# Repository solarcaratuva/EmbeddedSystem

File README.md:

# UVA Solar Car Team Electrical Team - Embedded System Subgroup
The embedded system sub-group focuses on developing the embedded system for the solar car that controls the CAN bus, driver interface and BPS (Battery Management System). This repository contains all of the design files necessary to implement the electrical control systems necessary for the Solar Car project.

## ECU
The ECU is the primary controller for the majority of systems, including motor control, battery monitoring, driver interface, and MPPT interface. The PCB contains circuitry for interfacing buttons and switches on driver interface, high-current lights and horn, as well as

**!important!**
Not all pins are 12V or even 5V compatible. Certain pins connect directly to the teensy with no protection.

* signal: name of IO signal in Eeschema (may or may not also be the net name)
* voltage: the voltages the pin is designed for
* direction: The direction of the signal relative to the ECU
* description: description of the signal

### User interface input (control)
These pins are used for allowing the driver to command the vehicle. All but the UART pins are 12V logic. To reduce the number of pins required on the MCU, we chose to wire 3 way position switches such that the end contacts connect to the rails and the center contact floats with a resistor divider to ensure the voltage is approximately VCC/2 when the switch is in the middle position.

|      signal     | pin  | voltage  | direction |                            description                               |
|:---------------:|:----:|:--------:|:---------:|:--------------------------------------------------------------------:|
| BRAKE_CTRL      |  20  | 0 - 12V  |  input    | brake potentiometer, used to implement regen                         |
| REGEN_CTRL      |  17  | 0 - 12V  |  input    | regen potentiometer, used to set max regen percentage                |
| GEARSHIFT_CTRL  |  14  | 0 - 12V  |  input    | 3 way position switch. 12V = forward, 6V = neutral, 0V = reverse     |
| TURNSIG_CTRL    |  15  | 0 - 12V  |  input    | 3 way position switch. 12V = forward, 6V = neutral, 0V = reverse     |
| THROTTLE_CTRL   |  16  | 0 - 12V  |  input    | throttle potentiometer, the gas petal                                |
| STEER_CTRL      |21(A7)| 0 - 12V  |  input    | potentiometer on steering wheel, may be used for differential throttle control |
| HAZARD_CTRL     |  16  | 0 - 12V  |  input    | pushbutton used to activate hazard lights, toggles on changing edge  |
| HORN_CTRL       |22(A6)| 0 - 12V  |  input    | horn button                                                          |
| DOWN_CTRL       |  26  | 0 - 12V  |  input    | GUI navigation pushbutton                                            |
| UP_CTRL         |  27  | 0 - 12V  |  input    | GUI navigation pushbutton                                            |
| SEL_CTRL        |  28  | 0 - 12V  |  input    | GUI navigation pushbutton                                            |
| KILL_SENSE      |   2  | 0 - 12V  |  input    | used to detect if the power engaging the relays has been cut         |
| HAZARD_LED      |  25  | 0 - 12V  |  output   | connected to hazard button LED                                       |
| UART_1_RX       |   0  | 0 - 3.3V |  input    | used for Nextion 3.2" LCD                                            |
| UART_1_TX       |   1  | 0 - 3.3V |  output   | used for Nextion 3.2" LCD                                            |

### Serial interface IO
These pins are used for communicating with various peripherals, components, and subsystems within the car. CAN0 is reserved for the BMS, while CAN1 is used for all less critical systems. UART pins are for future use.

|      signal     |  pin    | voltage  | direction |                            description                               |
|:---------------:|:-------:|:--------:|:---------:|:--------------------------------------------------------------------:|
| CAN0_H          |         | 0 - 5V   | CAN high  | connected to CAN0 peripheral on Teensy 3.6 through MCP2562           |
| CAN0_L          |         | 0 - 5V   | CAN low   | connected to CAN0 peripheral on Teensy 3.6 through MCP2562           |
| CAN1_H          |         | 0 - 5V   | CAN high  | connected to CAN1 peripheral on Teensy 3.6 through MCP2562           |
| CAN1_L          |         | 0 - 5V   | CAN low   | connected to CAN1 peripheral on Teensy 3.6 through MCP2562           |
| UART_3_RX       |    7    | 0 - 3.3V |  input    | reserved for future use                                              |
| UART_3_TX       |    8    | 0 - 3.3V |  output   | reserved for future use                                              |
| UART_6_RX       |   47    | 0 - 3.3V |  input    | reserved for future use                                              |
| UART_6_TX       |   48    | 0 - 3.3V |  output   | reserved for future use                                              |

### Lights and Horn
These pins are capable of high currents (up to 5A distributed among the 4 outputs)

|      signal     |   pin    | voltage  | direction |                            description                               |
|:---------------:|:--------:|:--------:|:---------:|:--------------------------------------------------------------------:|
| HORN            |    57    | 0 - 12V  |   output  | high power output for car horn (can only source current)             |
| HEADLIGHTS      |    42    | 0 - 12V  |   output  | high power output for headlights (can only source current)           |
| BRAKELIGHTS     |    56    | 0 - 12V  |   output  | high power output for brakelights (can only source current)          |
| STROBE          |    6     | 0 - 12V  |   output  | high power output for strobelight (can only source current)          |
| RIGHT_BLINKERS  |    41    | 0 - 12V  |   output  | high power output for right blinkers (can only source current)       |
| LEFT_BLINKERS   |    40    | 0 - 12V  |   output  | high power output for left blinkers (can only source current)        |
| HORN_CTRL       |    22    | 0 - 12V  |   input   | high power input for horn                                            |
| HEADLIGHT_CTRL  |    23    | 0 - 12V  |   input   | high power input for headlights                                      |
| BRAKE_CTRL      |    20    | 0 - 12v  |   input   | analog input for brakes (used for regen)                             |

### Motor control
The motor can be interfaced via UART, CAN, and GPIO. As of now, we do not have any API or knowledge of how to interface the motor over UART, as it is not documented. However it is possible to decompile the android app and reverse engineer whatever the app implements. For now, we are using CAN to retrieve important parameters from the motor such as voltage, current, RPM, throttle, and error codes. The motor only outputs messages over CAN, and does not interpret them.

The table below holds true for both `MOTOR_R*` and `MOTOR_L*` signals.
NOTE: all node names in the table below are preceded with `MOTOR_R*` and `MOTOR_L*`!

|      signal     | pin (L) | pin (R) |  voltage   | direction |                               description                            |
|:---------------:|:--------|:-------:|:----------:|:---------:|:--------------------------------------------------------------------:|
| REGEN_EN        |   50    |   53    |   0 - 12V  |   output  | enables regenerative braking on motor controller                     |
| REGEN           | 36(pwm) | 37(pwm) |   0 - 5V   |   output  | analog output sets regen level when throttle is disabled (????)      |
| THROTTLE        | 35(pwm) | 38(pwm) |   0 - 5V   |   output  | sets throttle when FWD_EN or REV_EN are enabled.                     |
| ECO_EN          |   49    |   39    |   0 - 12V  |   output  | Reduces maximum power of motor controller                            |
| METER           |   A11   |   A10   |   0 - 12V  |   input   | analog output from motor controller (????)                           |
| FWD_EN          |   55    |   52    |   0 - 12V  |   output  | forward enable                                                       |
| REV_EN          |   54    |   51    |   0 - 12V  |   output  | reverse enable                                                       |

## Software
At the moment we have bits and pieces of code written but no unified project as of yet. The CAN repository contains experemantal code for interfacing the CAN peripherals on the Teensy as well as development towards a motor driver. The completed motor driver will eventually be refactored into this repo.

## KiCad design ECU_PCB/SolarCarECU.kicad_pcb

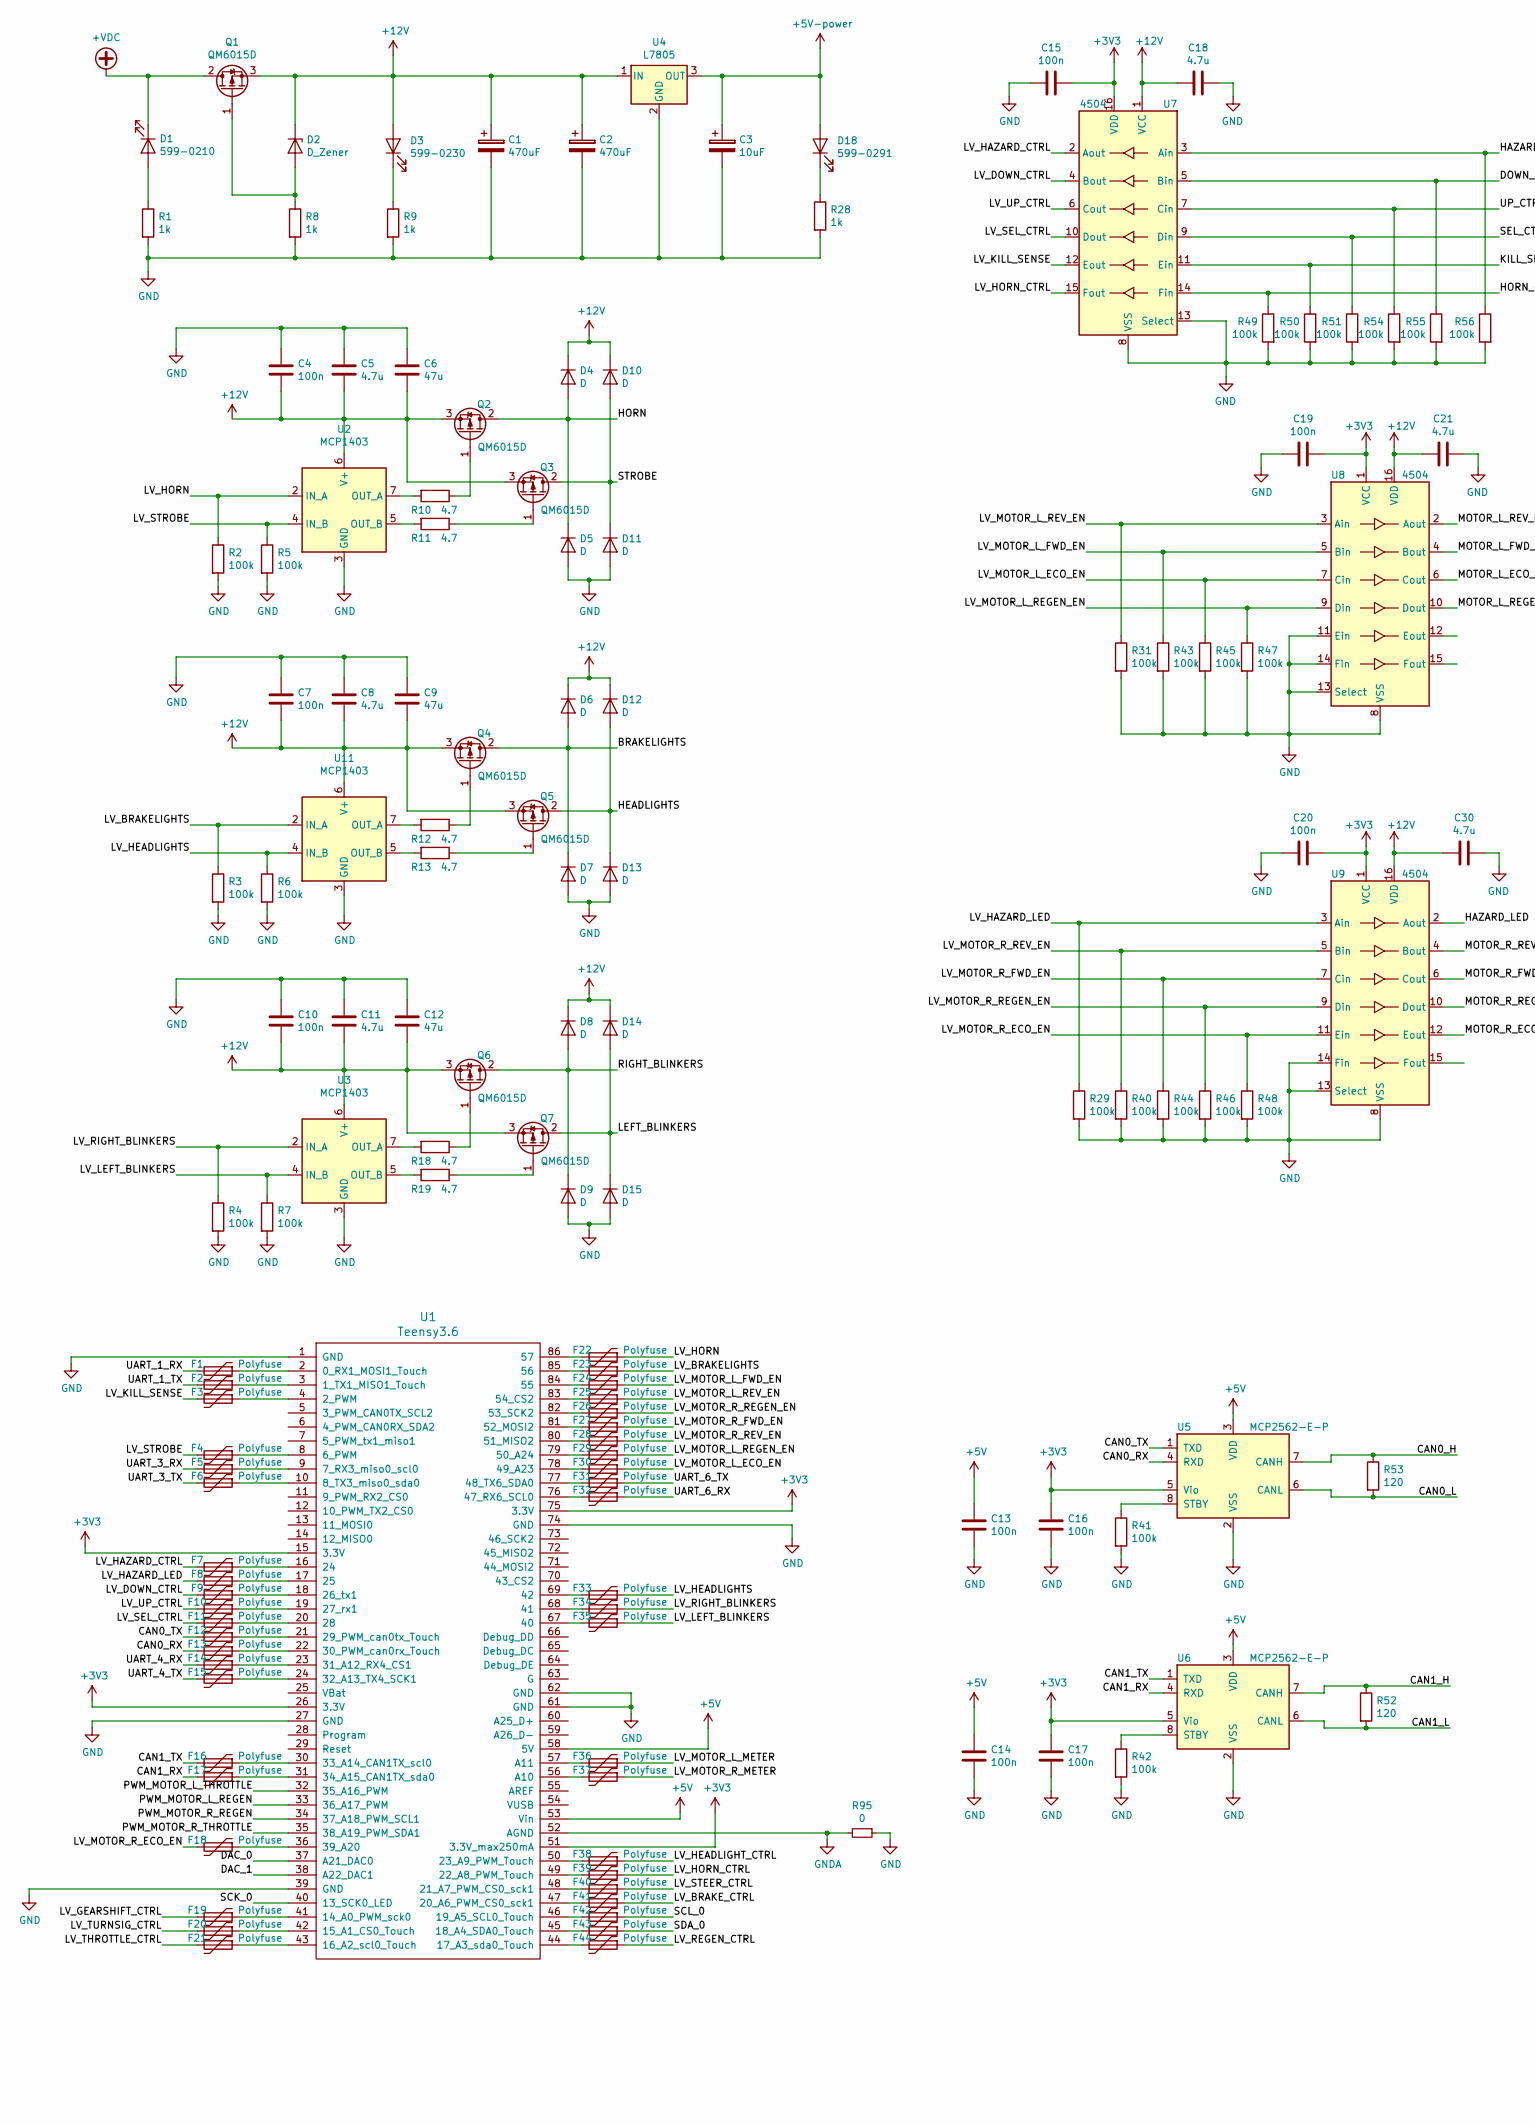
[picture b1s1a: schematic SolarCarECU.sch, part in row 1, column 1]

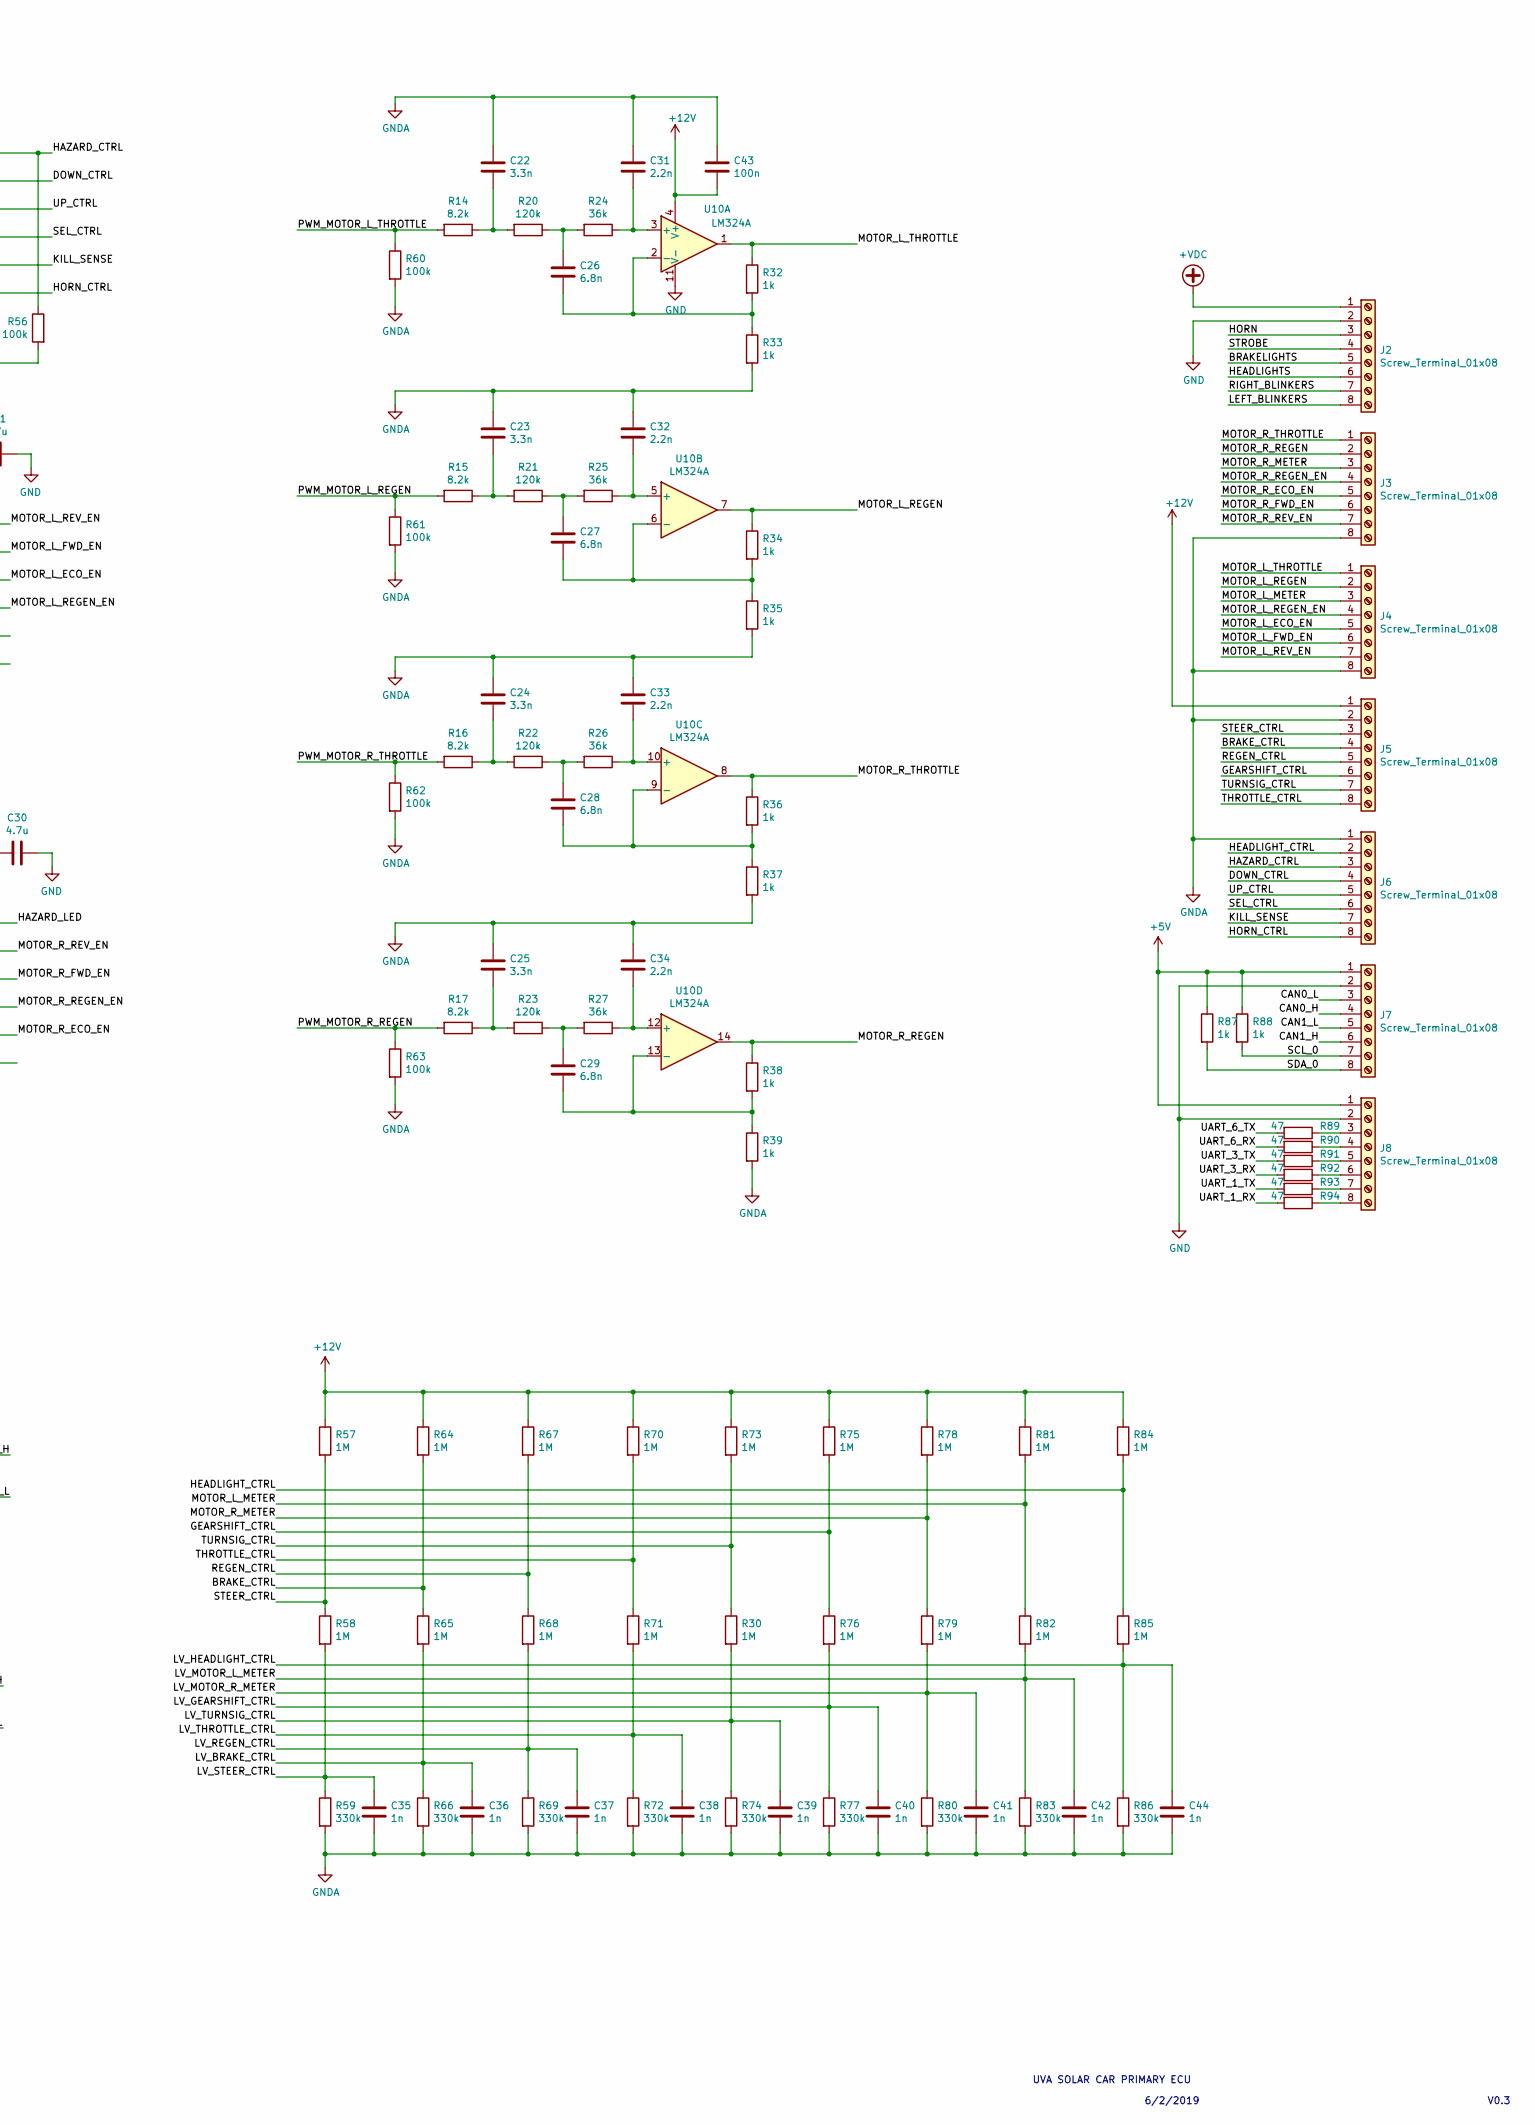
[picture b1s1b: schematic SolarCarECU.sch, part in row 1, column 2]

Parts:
C1, C2: 470uF; CP_Radial_D13.0mm_P5.00mm
C3: 10uF; C_1206_3216Metric
C4, C7, C10, C13, C14, C15, C16, C17, C19, C20, C43: 100n; C_1206_3216Metric
C5, C8, C11, C18, C21, C30: 4.7u; C_1206_3216Metric
C6, C9, C12: 47u; C_1206_3216Metric
C22, C23, C24, C25: 3.3n; C_0603_1608Metric
C26, C27, C28, C29: 6.8n; C_0603_1608Metric
C31, C32, C33, C34: 2.2n; C_0603_1608Metric
C35, C36, C37, C38, C39, C40, C41, C42, C44: 1n; C_0603_1608Metric
D1: 599-0210; LED_1206_3216Metric
D2: D_Zener; D_SOD-123
D3: 599-0230; LED_1206_3216Metric
D4, D5, D6, D7, D8, D9, D10, D11, D12, D13, D14, D15: D; D_SOD-123
D18: 599-0291; LED_1206_3216Metric
F1, F2, F3, F4, F5, F6, F7, F8, F9, F10, F11, F12, F13, F14, F15, F16, F17, F18, F19, F20, F21, F22, F23, F24, F25, F26, F27, F28, F29, F30, F31, F32, F33, F34, F35, F36, F37, F38, F39, F40, F41, F42, F43, F44: Polyfuse; Fuse_0603_1608Metric
J2: Screw_Terminal_01x08; PhoenixContact_MCV_1,5_8-G-5.08_1x08_P5.08mm_Vertical
J3, J4, J5, J6, J7, J8: Screw_Terminal_01x08; PinSocket_1x08_P2.54mm_Vertical
Q1, Q2, Q3, Q4, Q5, Q6, Q7: QM6015D; TO-252-2
R1, R8, R9, R28, R87, R88: 1k; R_1206_3216Metric
R2, R3, R4, R5, R6, R7, R41, R42: 100k; R_1206_3216Metric
R10, R11, R12, R13, R18, R19: 4.7; R_0603_1608Metric
R14, R15, R16, R17: 8.2k; R_0603_1608Metric
R20, R21, R22, R23: 120k; R_0603_1608Metric
R24, R25, R26, R27: 36k; R_0603_1608Metric
R29, R31, R40, R43, R44, R45, R46, R47, R48, R49, R50, R51, R54, R55, R56, R60, R61, R62, R63: 100k; R_0603_1608Metric
R30, R57, R58, R64, R65, R67, R68, R70, R71, R73, R75, R76, R78, R79, R81, R82, R84, R85: 1M; R_0603_1608Metric
R32, R33, R34, R35, R36, R37, R38, R39: 1k; R_0603_1608Metric
R52, R53: 120; R_1206_3216Metric
R59, R66, R69, R72, R74, R77, R80, R83, R86: 330k; R_0603_1608Metric
R89, R90, R91, R92, R93, R94: 47; R_0603_1608Metric
R95: 0; R_0603_1608Metric
U1: Teensy3.6; Teensy35_36
U2, U3, U11: MCP1403; DIP-8_W7.62mm
U4: L7805; PT78NR112H
U5, U6: MCP2562-E-P; DIP-8_W7.62mm
U7, U8, U9: 4504; SOIC-16_3.9x9.9mm_P1.27mm
U10: LM324A; SOIC-14_3.9x8.7mm_P1.27mm

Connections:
+3V3: C15.1, C16.1, C17.1, C19.1, C20.1, U1.15 (3.3V), U1.26 (3.3V), U1.51 (3.3V_max250mA), U1.75 (3.3V), U5.5 (Vio), U6.5 (Vio), U7.16 (VDD), U8.1 (VCC), U9.1 (VCC)
+12V: C1.1, C2.1, C4.2, C5.2, C6.2, C7.2, C8.2, C9.2, C10.2, C11.2, C12.2, C18.2, C21.2, C30.2, C43.2, D2.1 (K), D3.2 (A), D4.1 (K), D6.1 (K), D8.1 (K), D10.1 (K), D12.1 (K), D14.1 (K), J5.1, Q1.3 (S), Q2.3 (S), Q3.3 (S), Q4.3 (S), Q5.3 (S), Q6.3 (S), Q7.3 (S), R57.1, R64.1, R67.1, R70.1, R73.1, R75.1, R78.1, R81.1, R84.1, U2.6 (V+), U3.6 (V+), U4.1 (IN), U7.1 (VCC), U8.16 (VDD), U9.16 (VDD), U10.4 (V+), U11.6 (V+)
+VDC: D1.1 (K), J2.1, Q1.2 (D)
/BRAKELIGHTS: D6.2 (A), D7.1 (K), J2.5, Q4.2 (D)
/BRAKE_CTRL: J5.4, R64.2, R65.1
/CAN0_H: J7.4, R53.1, U5.7 (CANH)
/CAN0_L: J7.3, R53.2, U5.6 (CANL)
/CAN0_RX: F13.2, U5.4 (RXD)
/CAN0_TX: F12.2, U5.1 (TXD)
/CAN1_H: J7.6, R52.1, U6.7 (CANH)
/CAN1_L: J7.5, R52.2, U6.6 (CANL)
/CAN1_RX: F17.2, U6.4 (RXD)
/CAN1_TX: F16.2, U6.1 (TXD)
/DAC_0: U1.37 (A21_DAC0)
/DAC_1: U1.38 (A22_DAC1)
/DOWN_CTRL: J6.4, R55.1, U7.5 (Bin)
/GEARSHIFT_CTRL: J5.6, R75.2, R76.1
/HAZARD_CTRL: J6.3, R56.1, U7.3 (Ain)
/HAZARD_LED: U9.2 (Aout)
/HEADLIGHTS: D12.2 (A), D13.1 (K), J2.6, Q5.2 (D)
/HEADLIGHT_CTRL: J6.2, R84.2, R85.1
/HORN: D4.2 (A), D5.1 (K), J2.3, Q2.2 (D)
/HORN_CTRL: J6.8, R49.1, U7.14 (Fin)
/KILL_SENSE: J6.7, R50.1, U7.11 (Ein)
/LEFT_BLINKERS: D14.2 (A), D15.1 (K), J2.8, Q7.2 (D)
/LV_BRAKELIGHTS: F23.1, R3.1, U11.2 (IN_A)
/LV_BRAKE_CTRL: C36.1, F41.1, R65.2, R66.1
/LV_DOWN_CTRL: F9.2, U7.4 (Bout)
/LV_GEARSHIFT_CTRL: C40.1, F19.2, R76.2, R77.1
/LV_HAZARD_CTRL: F7.2, U7.2 (Aout)
/LV_HAZARD_LED: F8.2, R29.1, U9.3 (Ain)
/LV_HEADLIGHTS: F33.1, R6.1, U11.4 (IN_B)
/LV_HEADLIGHT_CTRL: C44.1, F38.1, R85.2, R86.1
/LV_HORN: F22.1, R2.1, U2.2 (IN_A)
/LV_HORN_CTRL: F39.1, U7.15 (Fout)
/LV_KILL_SENSE: F3.2, U7.12 (Eout)
/LV_LEFT_BLINKERS: F35.1, R7.1, U3.4 (IN_B)
/LV_MOTOR_L_ECO_EN: F30.1, R45.1, U8.7 (Cin)
/LV_MOTOR_L_FWD_EN: F24.1, R43.1, U8.5 (Bin)
/LV_MOTOR_L_METER: C42.1, F36.1, R82.2, R83.1
/LV_MOTOR_L_REGEN_EN: F29.1, R47.1, U8.9 (Din)
/LV_MOTOR_L_REV_EN: F25.1, R31.1, U8.3 (Ain)
/LV_MOTOR_R_ECO_EN: F18.2, R48.1, U9.11 (Ein)
/LV_MOTOR_R_FWD_EN: F27.1, R44.1, U9.7 (Cin)
/LV_MOTOR_R_METER: C41.1, F37.1, R79.2, R80.1
/LV_MOTOR_R_REGEN_EN: F26.1, R46.1, U9.9 (Din)
/LV_MOTOR_R_REV_EN: F28.1, R40.1, U9.5 (Bin)
/LV_REGEN_CTRL: C37.1, F44.1, R68.2, R69.1
/LV_RIGHT_BLINKERS: F34.1, R4.1, U3.2 (IN_A)
/LV_SEL_CTRL: F11.2, U7.10 (Dout)
/LV_STEER_CTRL: C35.1, F40.1, R58.2, R59.1
/LV_STROBE: F4.2, R5.1, U2.4 (IN_B)
/LV_THROTTLE_CTRL: C38.1, F21.2, R71.2, R72.1
/LV_TURNSIG_CTRL: C39.1, F20.2, R30.2, R74.1
/LV_UP_CTRL: F10.2, U7.6 (Cout)
/MOTOR_L_ECO_EN: J4.5, U8.6 (Cout)
/MOTOR_L_FWD_EN: J4.6, U8.4 (Bout)
/MOTOR_L_METER: J4.3, R81.2, R82.1
/MOTOR_L_REGEN: J4.2, R34.1, U10.7
/MOTOR_L_REGEN_EN: J4.4, U8.10 (Dout)
/MOTOR_L_REV_EN: J4.7, U8.2 (Aout)
/MOTOR_L_THROTTLE: J4.1, R32.1, U10.1
/MOTOR_R_ECO_EN: J3.5, U9.12 (Eout)
/MOTOR_R_FWD_EN: J3.6, U9.6 (Cout)
/MOTOR_R_METER: J3.3, R78.2, R79.1
/MOTOR_R_REGEN: J3.2, R38.1, U10.14
/MOTOR_R_REGEN_EN: J3.4, U9.10 (Dout)
/MOTOR_R_REV_EN: J3.7, U9.4 (Bout)
/MOTOR_R_THROTTLE: J3.1, R36.1, U10.8
/PWM_MOTOR_L_REGEN: R15.2, R61.1, U1.33 (36_A17_PWM)
/PWM_MOTOR_L_THROTTLE: R14.2, R60.1, U1.32 (35_A16_PWM)
/PWM_MOTOR_R_REGEN: R17.2, R63.1, U1.34 (37_A18_PWM_SCL1)
/PWM_MOTOR_R_THROTTLE: R16.2, R62.1, U1.35 (38_A19_PWM_SDA1)
/REGEN_CTRL: J5.5, R67.2, R68.1
/RIGHT_BLINKERS: D8.2 (A), D9.1 (K), J2.7, Q6.2 (D)
/SCK_0: U1.40 (13_SCK0_LED)
/SCL_0: F42.1, J7.7, R88.2
/SDA_0: F43.1, J7.8, R87.2
/SEL_CTRL: J6.6, R51.1, U7.9 (Din)
/STEER_CTRL: J5.3, R57.2, R58.1
/STROBE: D10.2 (A), D11.1 (K), J2.4, Q3.2 (D)
/THROTTLE_CTRL: J5.8, R70.2, R71.1
/TURNSIG_CTRL: J5.7, R30.1, R73.2
/UART_1_RX: F1.2, R94.2
/UART_1_TX: F2.2, R93.2
/UART_3_RX: F5.2, R92.2
/UART_3_TX: F6.2, R91.2
/UART_4_RX: F14.2
/UART_4_TX: F15.2
/UART_6_RX: F32.1, R90.2
/UART_6_TX: F31.1, R89.2
/UP_CTRL: J6.5, R54.1, U7.7 (Cin)
GND: C1.2, C2.2, C3.2, C4.1, C5.1, C6.1, C7.1, C8.1, C9.1, C10.1, C11.1, C12.1, C13.2, C14.2, C15.2, C16.2, C17.2, C18.1, C19.2, C20.2, C21.1, C30.1, D5.2 (A), D7.2 (A), D9.2 (A), D11.2 (A), D13.2 (A), D15.2 (A), J2.2, J7.2, J8.2, R1.2, R2.2, R3.2, R4.2, R5.2, R6.2, R7.2, R8.2, R9.2, R28.2, R29.2, R31.2, R40.2, R41.2, R42.2, R43.2, R44.2, R45.2, R46.2, R47.2, R48.2, R49.2, R50.2, R51.2, R54.2, R55.2, R56.2, R95.1, U1.1 (GND), U1.27 (GND), U1.39 (GND), U1.61 (GND), U1.62 (GND), U1.74 (GND), U2.3 (GND), U3.3 (GND), U4.2 (GND), U5.2 (VSS), U6.2 (VSS), U7.8 (VSS), U7.13 (Select), U8.8 (VSS), U8.11 (Ein), U8.13 (Select), U8.14 (Fin), U9.8 (VSS), U9.13 (Select), U9.14 (Fin), U10.11 (V-), U11.3 (GND); also elsewhere on the board
GNDA: C22.2, C23.2, C24.2, C25.2, C31.1, C32.1, C33.1, C34.1, C35.2, C36.2, C37.2, C38.2, C39.2, C40.2, C41.2, C42.2, C43.1, C44.2, J3.8, J4.8, J5.2, J6.1, R33.2, R35.2, R37.2, R39.2, R59.2, R60.2, R61.2, R62.2, R63.2, R66.2, R69.2, R72.2, R74.2, R77.2, R80.2, R83.2, R86.2, R95.2, U1.52 (AGND); also elsewhere on the board
unnamed: C22.1, R14.1, R20.2
unnamed: C23.1, R15.1, R21.2
unnamed: C24.1, R16.1, R22.2
unnamed: C25.1, R17.1, R23.2
unnamed: C26.1, R20.1, R24.2
unnamed: C26.2, R32.2, R33.1, U10.2 (-)
unnamed: C27.1, R21.1, R25.2
unnamed: C27.2, R34.2, R35.1, U10.6 (-)
unnamed: C28.1, R22.1, R26.2
unnamed: C28.2, R36.2, R37.1, U10.9 (-)
unnamed: C29.1, R23.1, R27.2
unnamed: C29.2, R38.2, R39.1, U10.13 (-)
unnamed: C31.2, R24.1, U10.3 (+)
unnamed: C32.2, R25.1, U10.5 (+)
unnamed: C33.2, R26.1, U10.10 (+)
unnamed: C34.2, R27.1, U10.12 (+)
unnamed: D1.2 (A), R1.1
unnamed: D2.2 (A), Q1.1 (G), R8.1
unnamed: D3.1 (K), R9.1
unnamed: D18.1 (K), R28.1
unnamed: F1.1, U1.2 (0_RX1_MOSI1_Touch)
unnamed: F2.1, U1.3 (1_TX1_MISO1_Touch)
unnamed: F3.1, U1.4 (2_PWM)
unnamed: F4.1, U1.8 (6_PWM)
unnamed: F5.1, U1.9 (7_RX3_miso0_scl0)
unnamed: F6.1, U1.10 (8_TX3_miso0_sda0)
unnamed: F7.1, U1.16 (24)
unnamed: F8.1, U1.17 (25)
unnamed: F9.1, U1.18 (26_tx1)
unnamed: F10.1, U1.19 (27_rx1)
unnamed: F11.1, U1.20 (28)
unnamed: F12.1, U1.21 (29_PWM_can0tx_Touch)
unnamed: F13.1, U1.22 (30_PWM_can0rx_Touch)
unnamed: F14.1, U1.23 (31_A12_RX4_CS1)
unnamed: F15.1, U1.24 (32_A13_TX4_SCK1)
unnamed: F16.1, U1.30 (33_A14_CAN1TX_scl0)
unnamed: F17.1, U1.31 (34_A15_CAN1TX_sda0)
unnamed: F18.1, U1.36 (39_A20)
unnamed: F19.1, U1.41 (14_A0_PWM_sck0)
unnamed: F20.1, U1.42 (15_A1_CS0_Touch)
unnamed: F21.1, U1.43 (16_A2_scl0_Touch)
unnamed: F22.2, U1.86 (57)
unnamed: F23.2, U1.85 (56)
unnamed: F24.2, U1.84 (55)
unnamed: F25.2, U1.83 (54_CS2)
unnamed: F26.2, U1.82 (53_SCK2)
unnamed: F27.2, U1.81 (52_MOSI2)
unnamed: F28.2, U1.80 (51_MISO2)
unnamed: F29.2, U1.79 (50_A24)
unnamed: F30.2, U1.78 (49_A23)
unnamed: F31.2, U1.77 (48_TX6_SDA0)
unnamed: F32.2, U1.76 (47_RX6_SCL0)
unnamed: F33.2, U1.69 (42)
unnamed: F34.2, U1.68 (41)
unnamed: F35.2, U1.67 (40)
unnamed: F36.2, U1.57 (A11)
unnamed: F37.2, U1.56 (A10)
unnamed: F38.2, U1.50 (23_A9_PWM_Touch)
unnamed: F39.2, U1.49 (22_A8_PWM_Touch)
unnamed: F40.2, U1.48 (21_A7_PWM_CS0_sck1)
unnamed: F41.2, U1.47 (20_A6_PWM_CS0_sck1)
unnamed: F42.2, U1.46 (19_A5_SCL0_Touch)
unnamed: F43.2, U1.45 (18_A4_SDA0_Touch)
unnamed: F44.2, U1.44 (17_A3_sda0_Touch)
unnamed: J8.3, R89.1
unnamed: J8.4, R90.1
unnamed: J8.5, R91.1
unnamed: J8.6, R92.1
unnamed: J8.7, R93.1
unnamed: J8.8, R94.1
unnamed: Q2.1 (G), R10.1
unnamed: Q3.1 (G), R11.1
unnamed: Q4.1 (G), R12.1
unnamed: Q5.1 (G), R13.1
unnamed: Q6.1 (G), R18.1
unnamed: Q7.1 (G), R19.1
unnamed: R10.2, U2.7 (OUT_A)
unnamed: R11.2, U2.5 (OUT_B)
unnamed: R12.2, U11.7 (OUT_A)
unnamed: R13.2, U11.5 (OUT_B)
unnamed: R18.2, U3.7 (OUT_A)
unnamed: R19.2, U3.5 (OUT_B)
unnamed: R41.1, U5.8 (STBY)
unnamed: R42.1, U6.8 (STBY)

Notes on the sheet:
UVA SOLAR CAR PRIMARY ECU
V0.3
6/2/2019

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
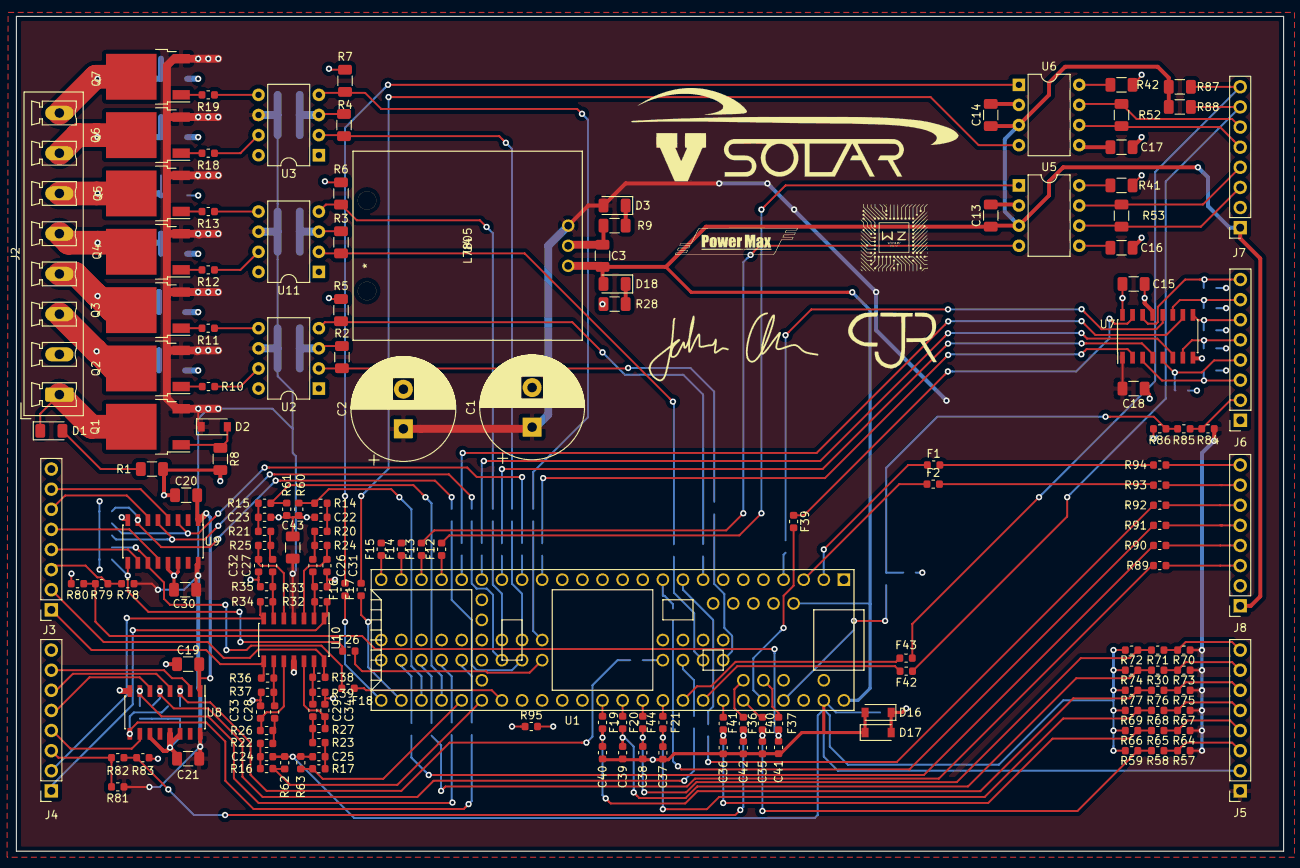
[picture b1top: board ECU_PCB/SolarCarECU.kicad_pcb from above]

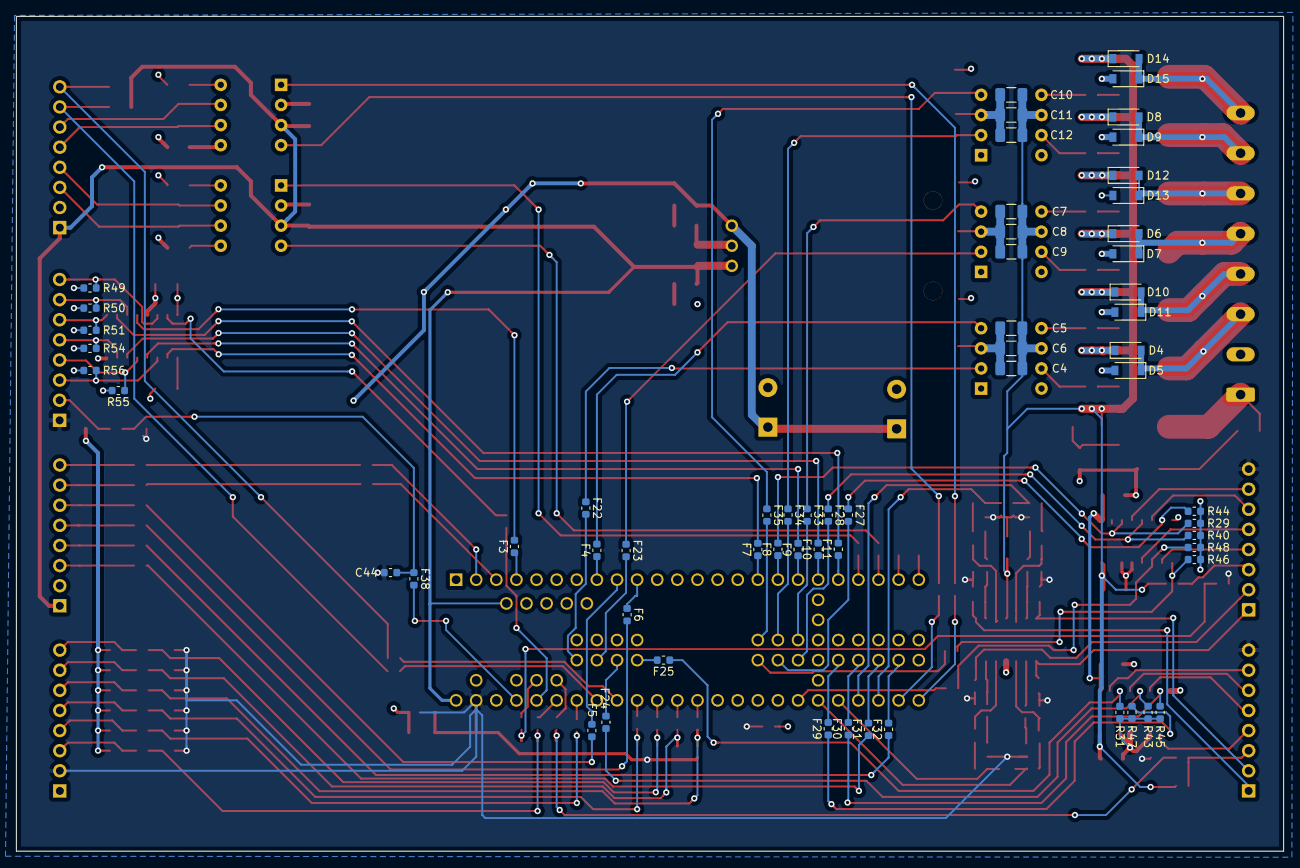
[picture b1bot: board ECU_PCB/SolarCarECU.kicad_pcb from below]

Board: 4 copper layers, 160.0 x 105.4 mm, 226 parts (60 on the bottom side), 173 nets.

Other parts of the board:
D16, D17: D; D_SOD-123

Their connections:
GND: D16.1, D17.2; also elsewhere on the board
GNDA: D16.2, D17.1; also elsewhere on the board

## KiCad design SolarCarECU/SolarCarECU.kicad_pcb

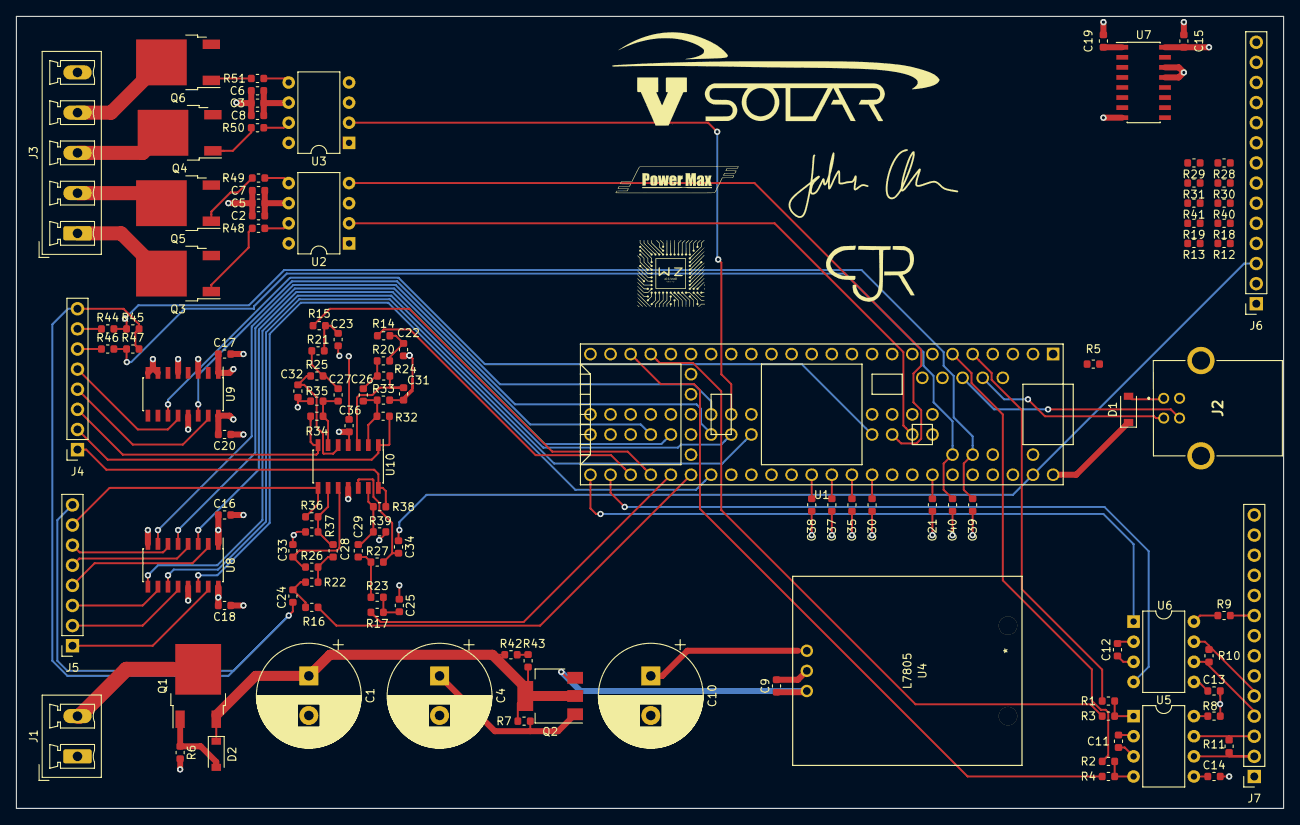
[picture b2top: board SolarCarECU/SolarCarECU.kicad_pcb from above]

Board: 4 copper layers, 160.0 x 100.0 mm, 116 parts (0 on the bottom side), 116 nets.

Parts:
C1, C4: 470uF; CP_Radial_D13.0mm_P5.00mm
C2, C3, C11, C12, C13, C14, C15, C16, C17, C36: 0.47u; C_0603_1608Metric
C5, C6, C18, C19, C20: 4.7u; C_0603_1608Metric
C7, C8: 47u; C_0603_1608Metric
C9: 10uF; C_0603_1608Metric
C10: 10uF; CP_Radial_D13.0mm_P5.00mm
C21, C30, C35, C37, C38, C39, C40: C; C_0603_1608Metric
C22, C23, C24, C25: 3.3n; C_0603_1608Metric
C26, C27, C28, C29: 6.8n; C_0603_1608Metric
C31, C32, C33, C34: 2.2n; C_0603_1608Metric
D1: D_Schottky; D_SOD-123
D2: D_Zener; D_SOD-123
J1: Screw_Terminal_01x02; PhoenixContact_MCV_1,5_2-G-5.08_1x02_P5.08mm_Vertical
J2: USB_B_Micro; USBRBSSOTH
J3: Screw_Terminal_01x05; PhoenixContact_MCV_1,5_5-G-5.08_1x05_P5.08mm_Vertical
J4, J5: Screw_Terminal_01x08; PinSocket_1x08_P2.54mm_Vertical
J6, J7: Screw_Terminal_01x14; PinSocket_1x14_P2.54mm_Vertical
Q1, Q3, Q4, Q5, Q6: QM6015D; TO-252-2
Q2: PZT2222A; SOT-223
R1, R2, R3, R4, R5, R42, R43: 0; R_0603_1608Metric
R6, R32, R33, R34, R35, R36, R37, R38, R39: 1k; R_0603_1608Metric
R7, R10, R11: 120; R_0603_1608Metric
R8, R9: 100k; R_0603_1608Metric
R12, R13, R18, R19, R28, R29, R30, R31, R40, R41, R44, R45, R46, R47: R; R_0603_1608Metric
R14, R15, R16, R17: 8.2k; R_0603_1608Metric
R20, R21, R22, R23: 120k; R_0603_1608Metric
R24, R25, R26, R27: 36k; R_0603_1608Metric
R48, R49, R50, R51: 4.7; R_0603_1608Metric
U1: Teensy3.6; Teensy35_36
U2, U3: EL7202CN; DIP-8_W7.62mm
U4: L7805; PT78NR112H
U5, U6: MCP2562-E-P; DIP-8_W7.62mm
U7, U8, U9: 4504; SOIC-16_3.9x9.9mm_P1.27mm
U10: LM324A; SOIC-14_3.9x8.7mm_P1.27mm

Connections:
+3V3: C13.1, C14.1, C15.1, C16.1, C17.1, U1.15, U1.26, U1.75, U5.5, U6.5, U7.16, U8.1, U9.1
+5V: C10.1, C11.1, C12.1, C36.2, D1.1, J6.1, J7.6, U1.53, U1.58, U4.3, U5.3, U6.3, U10.4
+12V: C2.2, C3.2, C5.2, C6.2, C7.2, C8.2, C18.2, C19.2, C20.2, J6.2, J7.1, Q3.3, Q4.3, Q5.3, Q6.3, R42.1, R43.1, U2.6, U3.6, U7.1, U8.16, U9.16
/BLINKERS: J3.4, Q6.2
/BRAKELIGHTS: J3.3, Q4.2
/BRAKE_CTRL: J6.4, R12.1
/CAN0_H: J7.3, R11.1, U5.7
/CAN0_L: J7.2, R11.2, U5.6
/CAN0_RX: R2.1, R4.1, U5.4
/CAN0_TX: R1.1, R3.1, U5.1
/CAN1_H: J7.5, R10.1, U6.7
/CAN1_L: J7.4, R10.2, U6.6
/CAN1_RX: U1.31, U6.4
/CAN1_TX: U1.30, U6.1
/CS_0: J7.10, U1.12
/DOWN_CTRL: J6.10, U7.5
/GEARSHIFT_CTRL: J6.6, R40.1
/HAZARD_CTRL: J6.9, U7.3
/HAZARD_LED: J6.14, U9.10
/HEADLIGHTS: J3.2, Q5.2
/HORN: J3.1, Q3.2
/KILL_SENSE: J6.13, U7.11
/LV_BLINKERS: U1.67, U3.4
/LV_BRAKELIGHTS: U1.68, U3.2
/LV_BRAKE_CTRL: C21.1, R12.2, R13.1, U1.47
/LV_DOWN_CTRL: U1.18, U7.4
/LV_GEARSHIFT_CTRL: C38.1, R40.2, R41.1, U1.41
/LV_HAZARD_CTRL: U1.16, U7.2
/LV_HAZARD_LED: U1.17, U9.9
/LV_HEADLIGHTS: U1.84, U2.4
/LV_HORN: U1.85, U2.2
/LV_MOTOR_L_ECO_EN: U1.78, U8.5
/LV_MOTOR_L_FWD_EN: U1.69, U9.14
/LV_MOTOR_L_METER: C40.1, R46.2, R47.1, U1.57
/LV_MOTOR_L_REGEN_EN: U1.79, U8.3
/LV_MOTOR_L_REV_EN: U1.83, U9.11
/LV_MOTOR_R_ECO_EN: U1.36, U8.14
/LV_MOTOR_R_FWD_EN: U1.81, U8.9
/LV_MOTOR_R_METER: C39.1, R44.2, R45.1, U1.56
/LV_MOTOR_R_REGEN_EN: U1.82, U8.11
/LV_MOTOR_R_REV_EN: U1.80, U8.7
/LV_REGEN_CTRL: C30.1, R18.2, R19.1, U1.44
/LV_SEL_CTRL: U1.20, U7.10
/LV_THROTTLE_CTRL: C35.1, R28.2, R29.1, U1.43
/LV_TURNSIG_CTRL: C37.1, R30.2, R31.1, U1.42
/LV_UP_CTRL: U1.19, U7.6
/MISO_0: J7.11, U1.13
/MOSI_0: J7.12, U1.14
/MOTOR_L_ECO_EN: J5.5, U8.4
/MOTOR_L_FWD_EN: J4.4, U9.15
/MOTOR_L_METER: J4.6, R46.1
/MOTOR_L_REGEN: J4.3, R34.1, U10.7
/MOTOR_L_REGEN_EN: J5.4, U8.2
/MOTOR_L_REV_EN: J4.5, U9.12
/MOTOR_L_THROTTLE: J4.2, R32.1, U10.1
/MOTOR_R_ECO_EN: J5.1, U8.15
/MOTOR_R_FWD_EN: J5.3, U8.10
/MOTOR_R_METER: J4.7, R44.1
/MOTOR_R_REGEN: J4.1, R38.1, U10.14
/MOTOR_R_REGEN_EN: J5.2, U8.12
/MOTOR_R_REV_EN: J5.6, U8.6
/MOTOR_R_THROTTLE: J5.7, R36.1, U10.8
/PWM_MOTOR_L_REGEN: R15.2, U1.33
/PWM_MOTOR_L_THROTTLE: R14.2, U1.32
/PWM_MOTOR_R_REGEN: R17.2, U1.34
/PWM_MOTOR_R_THROTTLE: R16.2, U1.35
/REGEN_CTRL: J6.5, R18.1
/SCK_0: J7.13, U1.40
/SEL_CTRL: J6.12, U7.9
/THROTTLE_CTRL: J6.8, R28.1
/TURNSIG_CTRL: J6.7, R30.1
/UART_RX: J7.7, U1.2
/UART_TX: J7.8, U1.3
/UP_CTRL: J6.11, U7.7
/USB_D+: J2.3, U1.60
/USB_D-: J2.2, U1.59
/USB_MASTER-SLAVE_SEL: R5.2, U1.86
GND: C1.2, C2.1, C3.1, C4.2, C5.1, C6.1, C7.1, C8.1, C9.2, C10.2, C11.2, C12.2, C13.2, C14.2, C15.2, C16.2, C17.2, C18.1, C19.1, C20.1, J1.1, J2.5, J2.6, J3.5, J7.9, J7.14, R6.2, R8.2, R9.2, U1.1, U1.27, U1.39, U1.61, U1.62, U1.74, U2.3, U3.3, U4.2, U5.2, U6.2, U7.8, U7.13, U7.14, U8.8, U8.13, U9.3, U9.5, U9.7, U9.8, U9.13, U10.11
GNDA: C21.2, C22.2, C23.2, C24.2, C25.2, C30.2, C31.1, C32.1, C33.1, C34.1, C35.2, C36.1, C37.2, C38.2, C39.2, C40.2, J4.8, J5.8, J6.3, R13.2, R19.2, R29.2, R31.2, R33.2, R35.2, R37.2, R39.2, R41.2, R45.2, R47.2, U1.52
unnamed: C1.1, D2.1, Q1.3, Q2.2, R7.1, R42.2, R43.2
unnamed: C4.1, Q2.1, R7.2
unnamed: C9.1, Q2.3, U4.1
unnamed: C22.1, R14.1, R20.2
unnamed: C23.1, R15.1, R21.2
unnamed: C24.1, R16.1, R22.2
unnamed: C25.1, R17.1, R23.2
unnamed: C26.1, R20.1, R24.2
unnamed: C26.2, R32.2, R33.1, U10.2
unnamed: C27.1, R21.1, R25.2
unnamed: C27.2, R34.2, R35.1, U10.6
unnamed: C28.1, R22.1, R26.2
unnamed: C28.2, R36.2, R37.1, U10.9
unnamed: C29.1, R23.1, R27.2
unnamed: C29.2, R38.2, R39.1, U10.13
unnamed: C31.2, R24.1, U10.3
unnamed: C32.2, R25.1, U10.5
unnamed: C33.2, R26.1, U10.10
unnamed: C34.2, R27.1, U10.12
unnamed: D1.2, J2.1
unnamed: D2.2, Q1.1, R6.1
unnamed: J1.2, Q1.2
unnamed: J2.4, R5.1
unnamed: Q3.1, R48.1
unnamed: Q4.1, R50.1
unnamed: Q5.1, R49.1
unnamed: Q6.1, R51.1
unnamed: R1.2, U1.5
unnamed: R2.2, U1.6
unnamed: R3.2, U1.21
unnamed: R4.2, U1.22
unnamed: R8.1, U5.8
unnamed: R9.1, U6.8
unnamed: R48.2, U2.7
unnamed: R49.2, U2.5
unnamed: R50.2, U3.7
unnamed: R51.2, U3.5

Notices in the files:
parts and their libraries:
Copyright 2016 Accelerated Designs. All rights reserved.
